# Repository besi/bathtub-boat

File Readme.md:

Bath tub boat
==============

Measure the temperature of your bath tub.
Video: https://vimeo.com/909430078

## Version 2

Pinout:

| Pin | Function             |
|----:|:---------------------|
|   0 | Boot mode / Switch 0 |
|   2 | Switch A             |
|   4 | Temp                 |
|   5 | I2C SCL              |
|  10 | I2C SDA              |
|   9 | Neopixel             |
|  14 | SPI CLK              |
|  15 | SPI CS               |
|  13 | SPI MOSI             |
|  12 | SPI MISO             |
| ADC | Light sensor         |

## Version 1

## Testing MQTT

    mosquitto_pub -h $MQTT_HOST -t 'services/bathtub' -u $MQTT_USER -P $MQTT_PASSWORD  -m '{"temp":41}' 
    mosquitto_pub -h $MQTT_HOST -t 'wled/all/col' -u $MQTT_USER -P $MQTT_PASSWORD  -m '#11ff00'

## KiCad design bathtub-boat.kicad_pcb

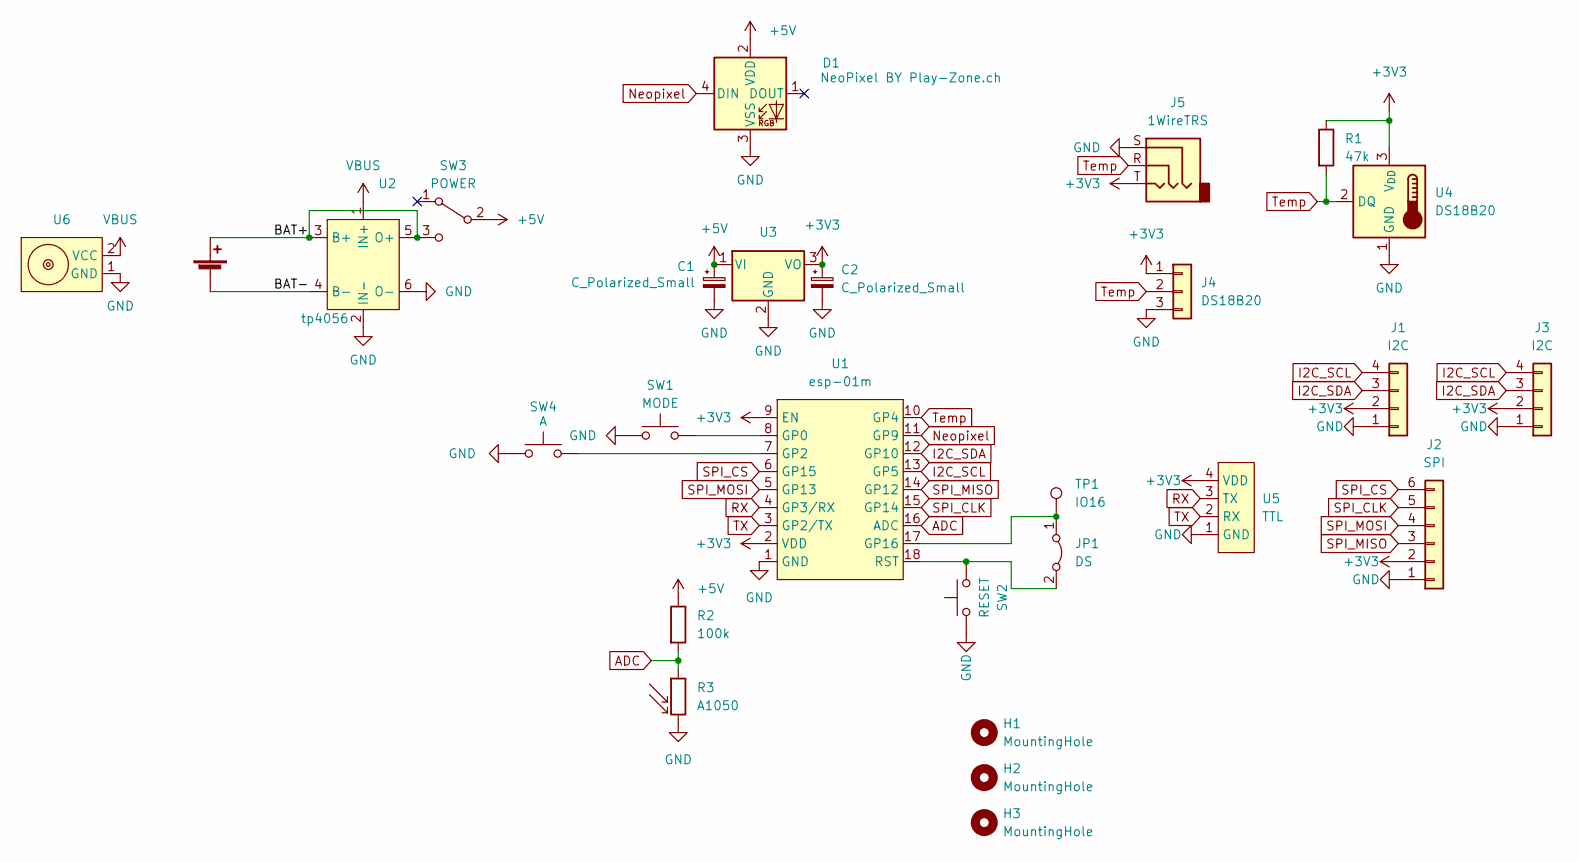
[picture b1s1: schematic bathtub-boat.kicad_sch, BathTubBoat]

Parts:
BT3: Battery_Cell; JST_PH_B2B-PH-K_1x02_P2.00mm_Vertical
C1, C2: C_Polarized_Small; CP_Radial_D5.0mm_P2.50mm
D1: NeoPixel BY Play-Zone.ch; LED_D5.0mm-4_RGB_Wide_Pins
H1, H2, H3: MountingHole; MountingHole_3.2mm_M3
J1: I2C; JST_SH_SM04B-SRSS-TB_1x04-1MP_P1.00mm_Horizontal
J2: SPI; PinHeader_1x06_P2.54mm_Vertical
J3: I2C; PinHeader_1x04_P2.54mm_Vertical
J4: DS18B20; JST_XH_B3B-XH-A_1x03_P2.50mm_Vertical
J5: 1WireTRS; Jack_3.5mm_CUI_SJ-3523-SMT_Horizontal
JP1: DS; SolderJumper-2_P1.3mm_Bridged_RoundedPad1.0x1.5mm
R1: 47k; R_Axial_DIN0207_L6.3mm_D2.5mm_P7.62mm_Horizontal
R2: 100k; R_Axial_DIN0207_L6.3mm_D2.5mm_P7.62mm_Horizontal
R3: A1050; R_LDR_4.9x4.2mm_P2.54mm_Vertical
SW1: MODE; pts636
SW2: RESET; pts636
SW3: POWER; as12ap
SW4: A; pts636
TP1: IO16; TestPoint_Pad_D1.0mm
U1: esp-01m
U2: tp4056
U3: UA78M33_TO252; TO-252-2
U4: DS18B20; TO-92_Inline
U5: TTL; PinHeader_1x04_P2.54mm_Vertical
U6: magnetic-charger

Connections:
+3V3: C2.1, J1.2, J2.2, J3.2, J4.1, J5.T, R1.1, U1.2 (VDD), U1.9 (EN), U3.3 (VO), U4.3 (V_{DD}), U5.4 (VDD)
+5V: C1.1, D1.2 (VDD), R2.1, SW3.2 (B), U3.1 (VI)
/BAT+: BT3.1 (+), SW3.3 (C), U2.3 (B+), U2.5 (O+)
/BAT-: BT3.2 (-), U2.4 (B-)
ADC: R2.2, R3.1, U1.16 (ADC)
GND: C1.2, C2.2, D1.3 (VSS), J1.1, J2.1, J3.1, J4.3, J5.S, R3.2, SW1.1, SW2.1, SW4.1, U1.1 (GND), U2.2 (IN-), U2.6 (O-), U3.2 (GND), U4.1 (GND), U5.1 (GND), U6.1 (GND)
I2C_SCL: J1.4, J3.4, U1.13 (GP5)
I2C_SDA: J1.3, J3.3, U1.12 (GP10)
Neopixel: D1.4 (DIN), U1.11 (GP9)
unnamed: JP1.1 (A), TP1.1, U1.17 (GP16)
unnamed: JP1.2 (B), SW2.2, U1.18 (RST)
unnamed: SW1.2, U1.8 (GP0)
unnamed: SW4.2, U1.7 (GP2)
RX: U1.4 (GP3/RX), U5.3 (TX)
SPI_CLK: J2.5, U1.15 (GP14)
SPI_CS: J2.6, U1.6 (GP15)
SPI_MISO: J2.3, U1.14 (GP12)
SPI_MOSI: J2.4, U1.5 (GP13)
TX: U1.3 (GP2/TX), U5.2 (RX)
Temp: J4.2, J5.R, R1.2, U1.10 (GP4), U4.2 (DQ)
VBUS: U2.1 (IN+), U6.2 (VCC)

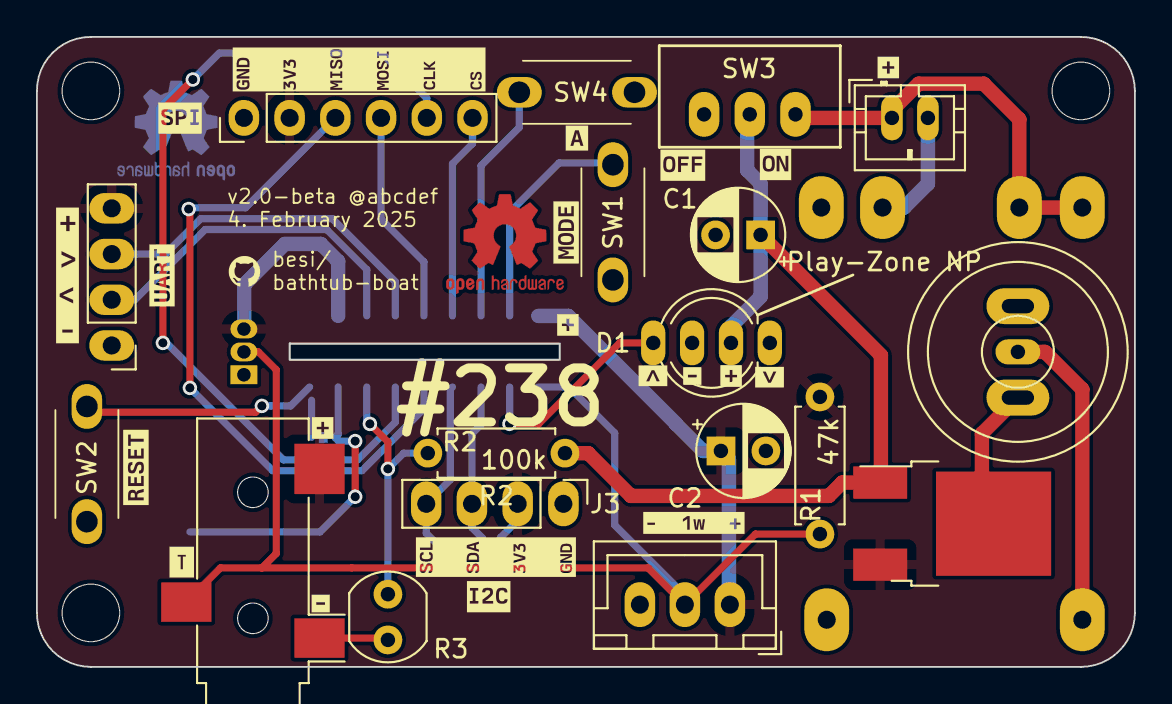
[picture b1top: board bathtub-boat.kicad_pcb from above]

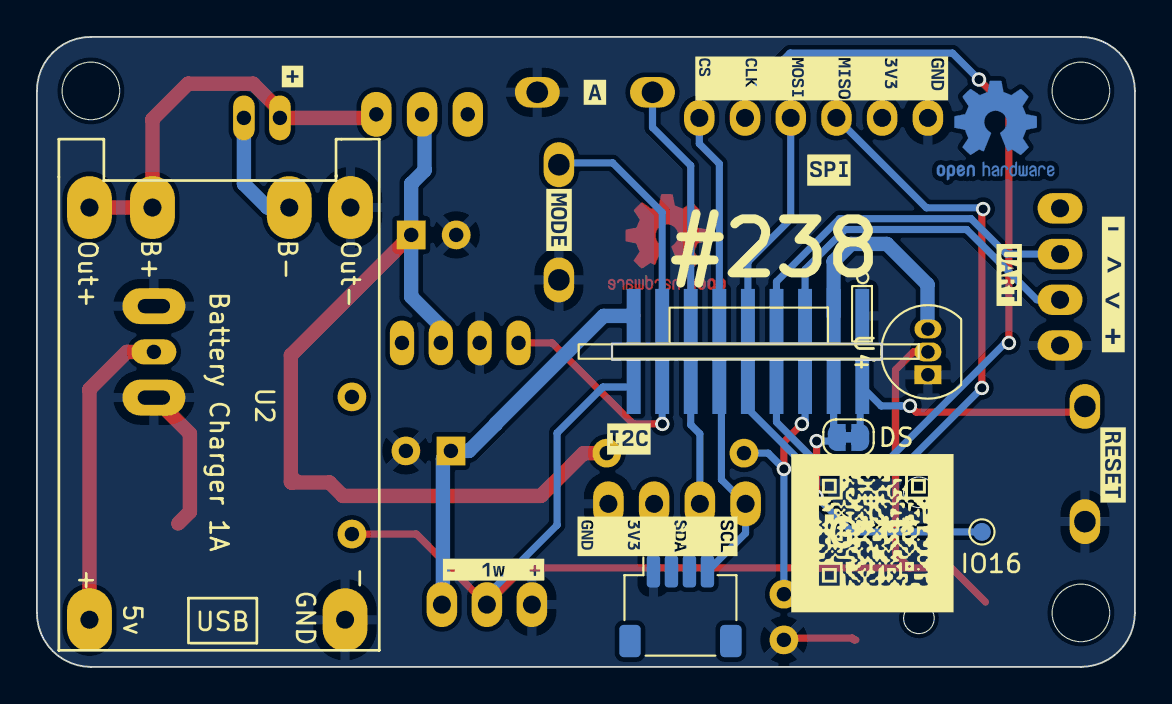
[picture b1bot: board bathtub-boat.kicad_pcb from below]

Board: 2 copper layers, 61.0 x 35.0 mm, 59 parts (17 on the bottom side), 21 nets.

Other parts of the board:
kibuzzard-65B8C3A2, kibuzzard-65B8C3A2#2: G***; kibuzzard-65B8C3A2
kibuzzard-65B8C65E, kibuzzard-65B8C65E#2: G***; kibuzzard-65B8C65E
kibuzzard-65B8C757, kibuzzard-65B8C757#2: G***; kibuzzard-65B8C757
kibuzzard-65B795B9, kibuzzard-65B795B9#2, kibuzzard-65B795B9#3, kibuzzard-65B795B9#4, kibuzzard-65B795B9#5: G***; kibuzzard-65B795B9
kibuzzard-65B796EF, kibuzzard-65B796EF#2: G***; kibuzzard-65B796EF
kibuzzard-65B796FD, kibuzzard-65B796FD#2: G***; kibuzzard-65B796FD
kibuzzard-65B7959E, kibuzzard-65B7959E#2: G***; kibuzzard-65B7959E
kibuzzard-65B7965E, kibuzzard-65B7965E#2: G***; kibuzzard-65B7965E
kibuzzard-65B79508, kibuzzard-65B79508#2: G***; kibuzzard-65B79508
kibuzzard-65B79597, kibuzzard-65B79597#2: G***; kibuzzard-65B79597
kibuzzard-65B98079: G***; kibuzzard-65B98079
kibuzzard-65B98083: G***; kibuzzard-65B98083
kibuzzard-65D6F389, kibuzzard-65D6F389#2: G***; kibuzzard-65D6F389
kibuzzard-65D7C44D, kibuzzard-65D7C44D#2: G***; kibuzzard-65D7C44D
kibuzzard-67A2929D: G***; kibuzzard-67A2929D
kibuzzard-679F7FF7, kibuzzard-679F7FF7#2: G***; kibuzzard-679F7FF7

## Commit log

2023-11-01 Add wifi capabilities
2023-11-01 Add MQTT library
2023-11-01 Setup simple MQTT
2023-11-01 Send the temperature over MQTT
2023-11-06 Show how to use the pasword in the secrets.example.py
2023-11-06 Set the delay to 5 seconds
2023-11-06 Bathtub temperature announcement
2023-11-06 Properly announce the temperature and startup the service at boot
2023-11-11 Only announce the temperature if the value changed to prevent spamming
2023-11-26 Set last will via mqtt
2023-11-26 Prevent 85 degrees at startup
2023-11-26 Log the temperature
2023-12-21 Initial pcb commit
2023-12-22 Add initial pcb
2023-12-22 Change path of tp4056 library
2023-12-22 ignore backup files
2024-01-04 Add components
2024-01-05 Prepare for milling
2024-01-22 Closer layout
2024-01-22 Add readme and fix 3d model of lipo charger
2024-01-22 Prepare the pcb for next iteration
2024-01-24 Minor changes to board, reflect tp4056 connections, todos for upcoming version
2024-01-24 Using the ESP8266 pcb and change the pin from 33 to 9
2024-01-24 Update the secrets.py with mqtt credentials
2024-01-30 New PCB version 2.0
2024-01-30 Updated software that waits for sensors
2024-01-30 Add power switch
2024-01-30 Update 3d model
2024-02-02 Ignore internal sensor if another is plugged in
2024-02-02 Fix last will message
2024-02-02 Post hello message
2024-02-02 Add LED indicator
2024-02-02 react to sensor changes and reset the announcement on new sensors
2024-02-03 Remove debuggin print statements
2024-02-03 Upload picture
2024-02-22 Production ready
2024-02-22 Add pullup resistor for optional parasitic power
2024-02-22 Update Silkscreen
2024-03-14 Deleted pts636
2024-03-14 Add pts636 library
2025-02-02 Add a top copper pour
2025-02-02 Round corners some silkscreen cleanup and a TRS Plug for the 1Wire connection
2025-02-04 Use special Play-Zone NeoPixel which has a different layout
2025-02-04 Final preparations for production
2025-02-04 Add measurements
2025-02-04 Add a DS18B20 that is facing downwards in the center for under water placement
2025-02-04 Change resistors, improve silkscreen and add OSHW logo
2025-02-04 Final tweaks prior to production
2025-02-04 Add solder jumper and testpoint for IO16
2025-02-04 Release 2.0
2025-03-01 Kicad 8
2025-03-04 New hardware
2025-03-07 Add pinout and fix schematic symbols
2025-12-18 Small improvements to the main.py file
2025-12-18 internal sensor hex
2025-12-18 Testing the sensor using mqtt
2026-01-22 Add startwifi
2026-01-22 Integrate with WLED
2026-01-24 Switch on any WLED enabled devices upon MQTT connection
2026-01-30 Update main script and adjust the temperature to 41
2026-01-30 Better handling of erroneous initial temperature readings
